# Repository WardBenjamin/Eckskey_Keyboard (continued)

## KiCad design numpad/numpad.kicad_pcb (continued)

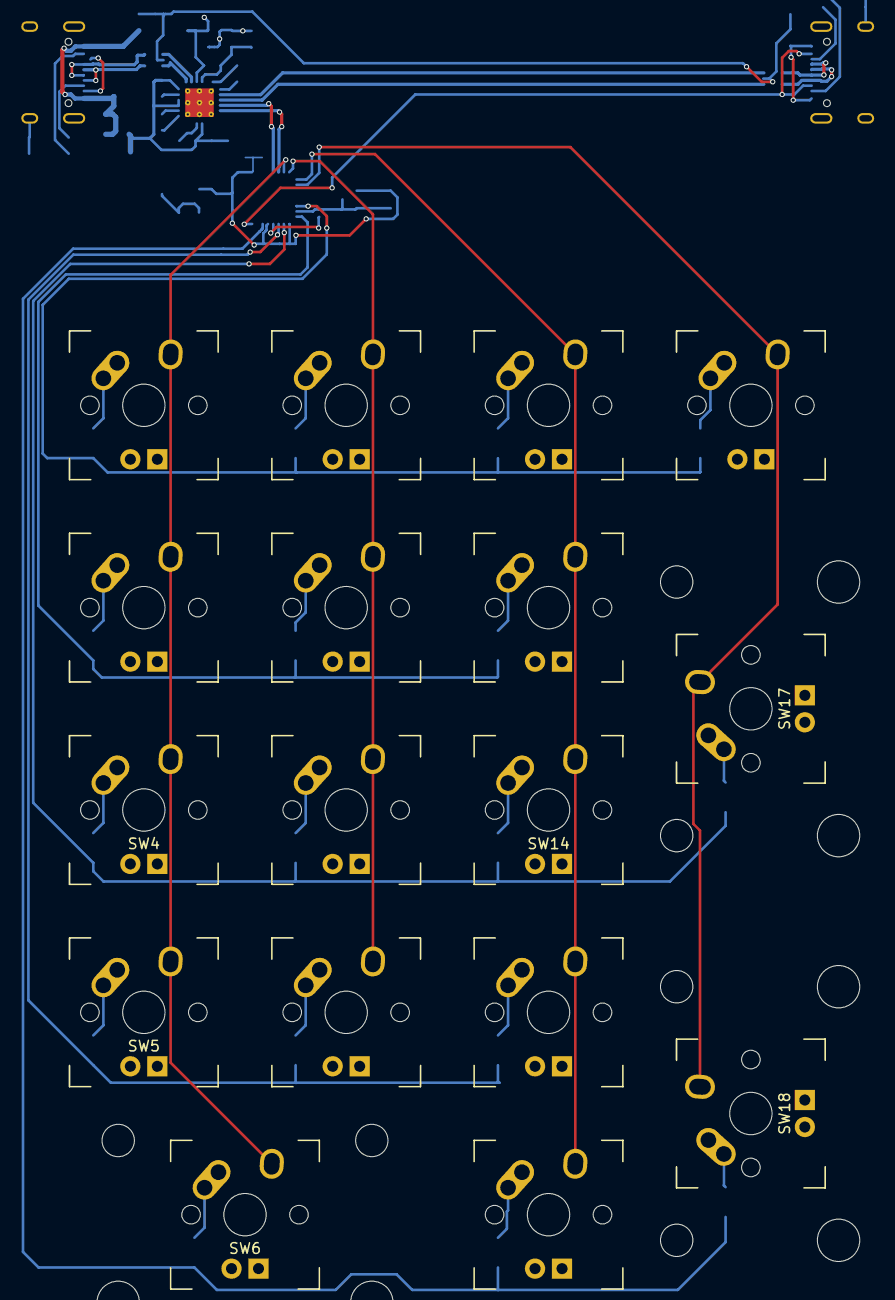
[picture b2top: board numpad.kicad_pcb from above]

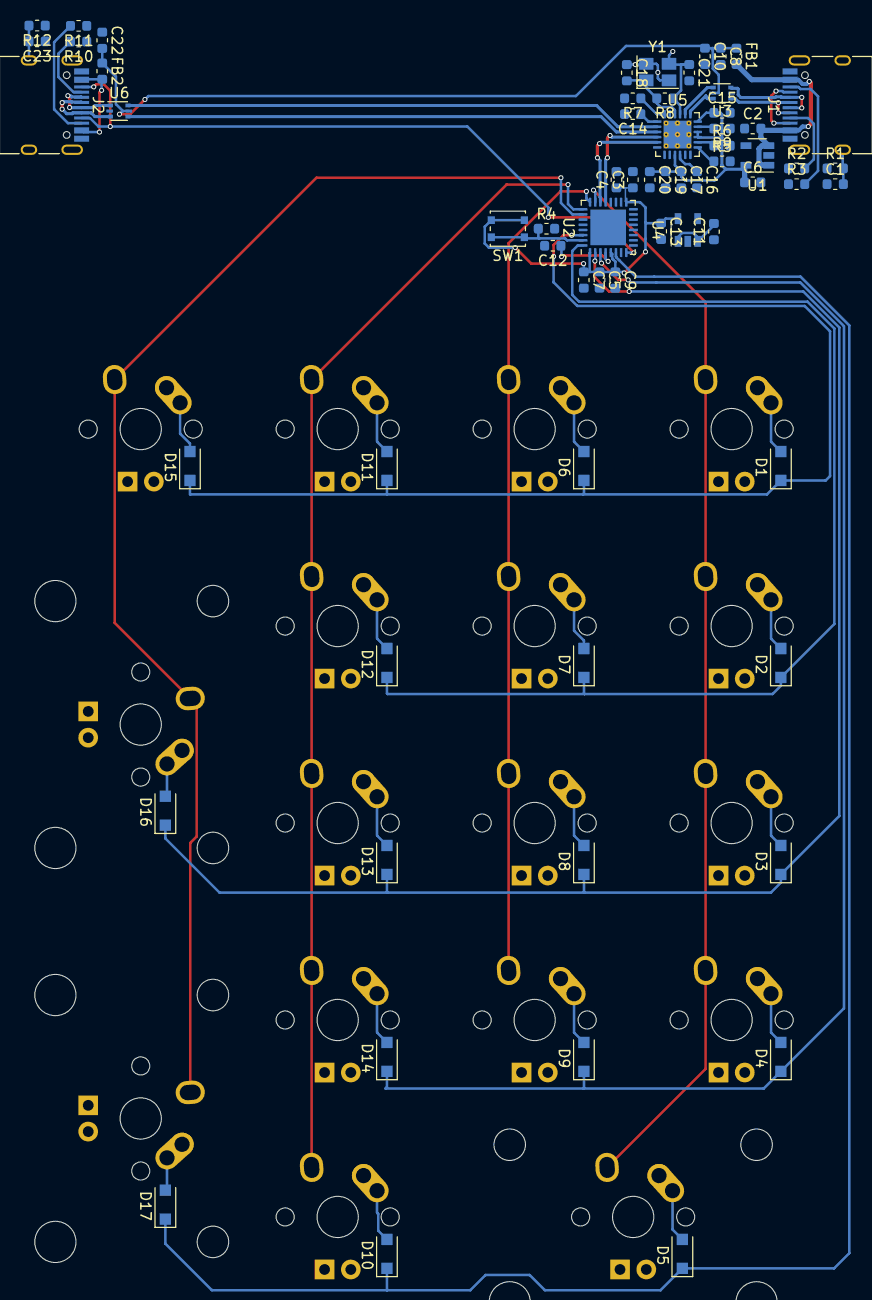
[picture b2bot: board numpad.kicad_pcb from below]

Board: 2 copper layers, 81 parts (64 on the bottom side), 58 nets.

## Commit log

2020-08-13 Initial commit; base keyboard 90% complete
2020-08-13 Add TODO notes to schematic
2020-08-13 Add README with project details
2020-08-14 Add base numpad files
2020-08-14 Route the rest of numpad
